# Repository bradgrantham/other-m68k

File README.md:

# other-m68k

A complete homebrew 68000 single-board computer: hardware, glue logic, firmware, SDK and
emulator, all generated from one specification.

| | |
|---|---|
| CPU | MC68000 at 12 MHz (24 MHz oscillator divided in the glue) |
| RAM | 1 MB: 2x AS6C4008-55PCN 512Kx8 SRAM, word wide, time-sliced with the video fetch |
| ROM | 1 MB window: 2x SST39SF040 flash, word wide; 256 KB BIOS image (in-system programmable, overlaid at address 0 at reset) plus a 768 KB FAT12 volume the BIOS mounts as drive C: |
| Video | memory-mapped 320x240, 8 bpp RGB332 framebuffer, two pages; AD724 encoder with composite and S-video outputs, NTSC (PAL by build option) |
| Glue | two ATF1508AS CPLDs ("MMU" and "I/O + shifter"), two 74AHCT245 bus transceivers |
| I/O | PS/2 keyboard, Atari joystick/paddle port (DE-9 on the DUART's I/O pins), microSD card on a bit-banged 4-bit SD bus, 68681 DUART serial on two FTDI headers (channel A at 38400 8N1 carries the POST and banner, then belongs to programs as `/dev/ttya`; channel B is free), 8-bit PDM audio (one byte per video line shifted out by the CPLD), 2 LEDs, NMI button |
| Power | USB-C, 5 V |

## Layout

| path | contents |
|---|---|
| `spec/board.json` | **the single source of truth**: memory map, registers, interrupts, video timing, syscalls, ABI |
| `tools/gen.py` | generates everything in `generated/` from the spec (`make gen`; `make check-gen` in CI) |
| `generated/` | C/asm headers, linker scripts, Verilog parameters, syscall stubs/dispatcher, emulator tables, `HARDWARE.md` |
| `docs/architecture.md` | the bus-timing contract: slot schedule, decode, alignment, peripherals |
| `docs/bringup.md` | staged hardware bring-up plan |
| `docs/programmers-guide.md` | programmer's guide: writing applications with the SDK, and programming the hardware directly |
| `hdl/` | Verilog for both CPLDs plus a system testbench with a 68000 bus model |
| `emu/` | SDL2 emulator (Musashi 68000 core), used to run the firmware and user programs |
| `fw/` | BIOS/monitor ROM: POST, serial, video console, PS/2, exceptions, monitor (drives C: and D:, scripts, AUTOEXEC.CMD), syscalls, FatFs with long names, flash volume driver, clock, ELF loader |
| `sdk/` | user-program crt0, linker script, syscall library, newlib shim, examples |
| `flashfs/` | the files that go into the C: volume besides the SDK examples (AUTOEXEC.CMD, README.TXT) |
| `kicad/` | generated schematic and PCB |

## Building

```
make gen        # regenerate from the spec
make fw         # fw/build/rom.bin (256 KB BIOS image, for the monitor's `flash` command)
make flash      # fw/build/flash.img (BIOS + the C: volume from flashfs/ and the SDK examples), rom_even.bin / rom_odd.bin for the two flash chips
make emu        # emu/build/m68k-emu
make sdk        # sdk/build/*.elf user programs
make run        # boot flash.img in the emulator (what the machine writes to C: persists in it)
make -C hdl sim # simulate the glue logic (needs iverilog)
```

Cross toolchain: `~/x-tools/m68k-unknown-elf` (crosstool-ng, GCC 15, `--with-cpu=68000`,
newlib). Override with `XTOOLS=/path/to/bin`.

## How the pieces fit

The spec names every address and bit once. `tools/gen.py` turns it into `hw.h` for C, `hw.inc`
for assembler, `board_params.vh` for the CPLDs, `emu_map.h` for the emulator and `HARDWARE.md`
for humans, plus syscall stubs for user programs and the dispatcher for the BIOS. Changing the
memory map or adding a syscall is one edit followed by `make gen`.

`docs/architecture.md` explains the mechanism the numbers describe: the SRAM is shared on a
fixed 4-clock slot, video takes the first half, the CPU the second, and CPU cycles are
phase-aligned by delaying DTACK by zero or two clocks. The video fetch therefore never costs
the CPU a bus slot.

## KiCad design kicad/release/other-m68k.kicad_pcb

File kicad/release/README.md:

# other-m68k release snapshot

Generated by `make -C kicad board route fab release` from the commit that last touched this directory.

- `other-m68k.kicad_pro` + `*.kicad_sch`: the schematic (open the .kicad_pro in KiCad 9; libraries resolve via ../lib)
- `other-m68k.kicad_pcb`: the **routed** board (DRC clean, 0 unrouted)
- `other-m68k-schematic.pdf`, `other-m68k-placement.svg`, `other-m68k-routed.svg`: for review without KiCad
- `fab/`: what PCBWay gets: `other-m68k-gerbers.zip`, `other-m68k-pcbway-bom.csv`, `other-m68k-pcbway-centroid.csv`;
  plus `other-m68k-customer-parts.csv` (what we fit), `other-m68k-bom-check.txt`, generic/JLCPCB BOMs

See ../ORDER.md for the order parameters.

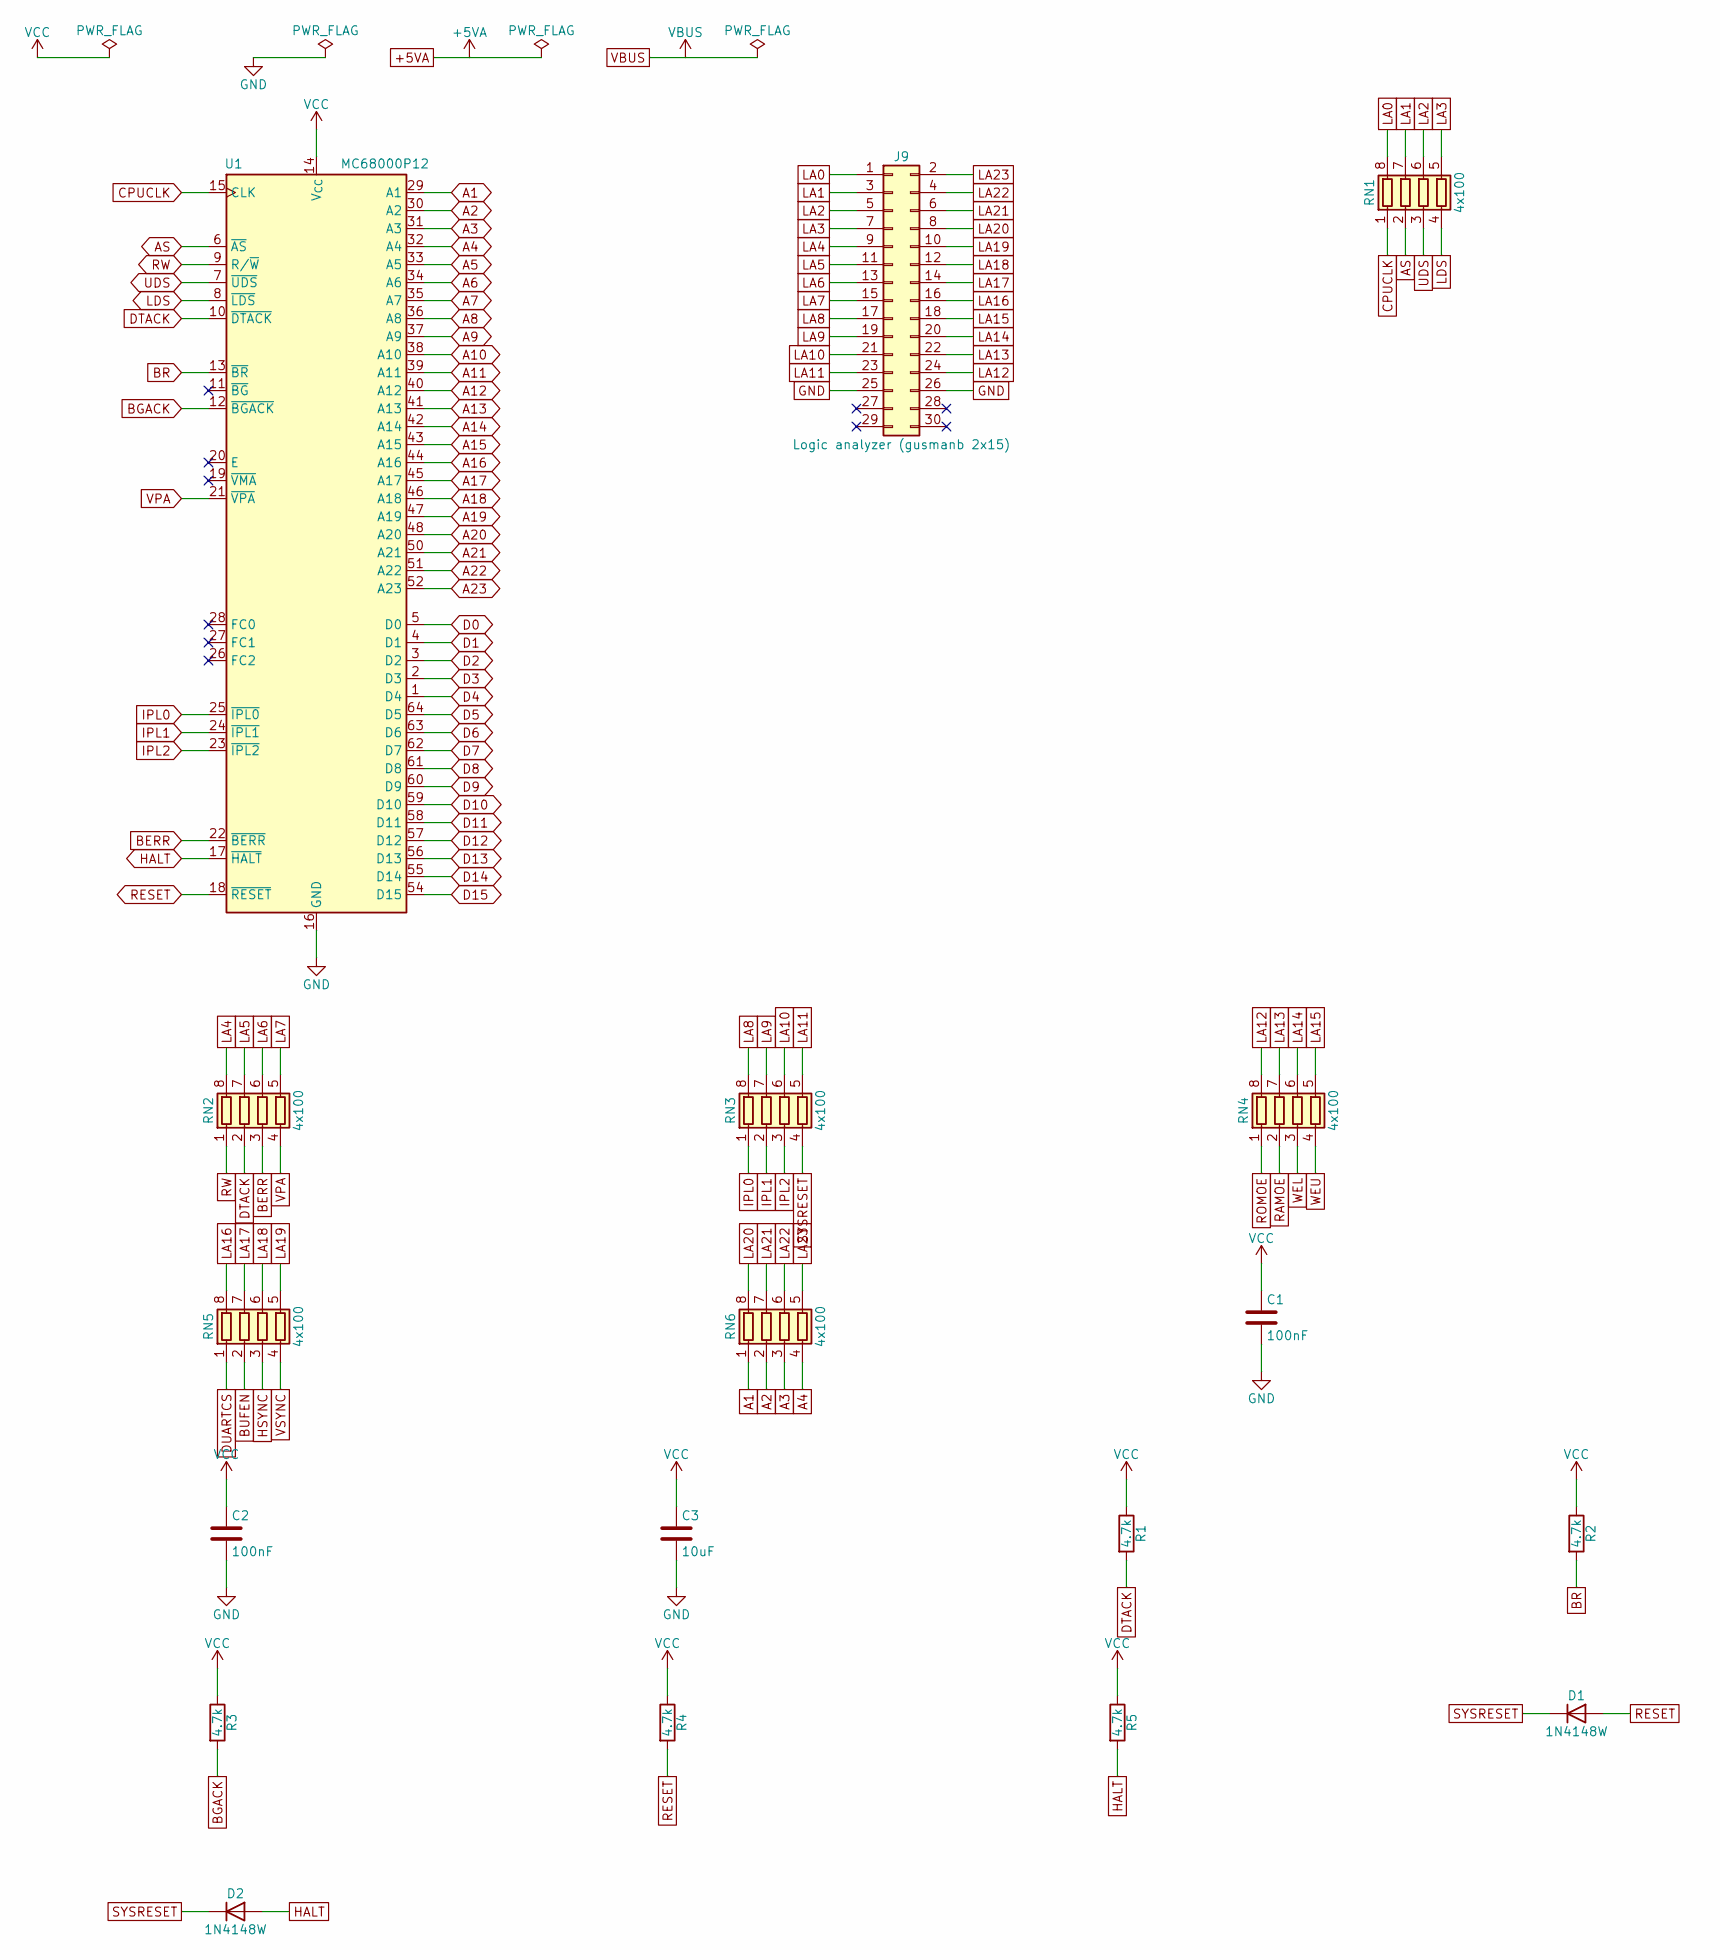
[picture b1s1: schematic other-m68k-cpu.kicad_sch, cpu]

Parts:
C1, C2: 100nF; C_0603_1608Metric; MPN CL10B104KB8NNNC; LCSC C1591
C3: 10uF; C_0805_2012Metric; MPN CL21A106KAYNNNE; LCSC C15850
D1, D2: 1N4148W; D_SOD-123; MPN 1N4148W-7-F; LCSC C81598
J9: Logic analyzer (gusmanb 2x15); PinHeader_2x15_P2.54mm_Vertical; MPN PRPC015DAAN-RC
R1, R2, R3, R4, R5: 4.7k; R_0603_1608Metric; MPN RC0603FR-074K7L; LCSC C23162
RN1, RN2, RN3, RN4, RN5, RN6: 4x100; R_Array_Convex_4x0603; MPN YC164-JR-07100RL
U1: MC68000P12; DIP-64_W22.86mm_Socket; MPN MC68000P12

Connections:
A1: RN6.1 (R1.1), U1.29 (A1); also elsewhere on the board
A2: RN6.2 (R2.1), U1.30 (A2); also elsewhere on the board
A3: RN6.3 (R3.1), U1.31 (A3); also elsewhere on the board
A4: RN6.4 (R4.1), U1.32 (A4); also elsewhere on the board
A5: U1.33 (A5); also elsewhere on the board
A6: U1.34 (A6); also elsewhere on the board
A7: U1.35 (A7); also elsewhere on the board
A8: U1.36 (A8); also elsewhere on the board
A9: U1.37 (A9); also elsewhere on the board
A10: U1.38 (A10); also elsewhere on the board
A11: U1.39 (A11); also elsewhere on the board
A12: U1.40 (A12); also elsewhere on the board
A13: U1.41 (A13); also elsewhere on the board
A14: U1.42 (A14); also elsewhere on the board
A15: U1.43 (A15); also elsewhere on the board
A16: U1.44 (A16); also elsewhere on the board
A17: U1.45 (A17); also elsewhere on the board
A18: U1.46 (A18); also elsewhere on the board
A19: U1.47 (A19); also elsewhere on the board
A20: U1.48 (A20); also elsewhere on the board
A21: U1.50 (A21); also elsewhere on the board
A22: U1.51 (A22); also elsewhere on the board
A23: U1.52 (A23); also elsewhere on the board
AS: RN1.2 (R2.1), U1.6 (~AS); also elsewhere on the board
BERR: RN2.3 (R3.1), U1.22 (~BERR); also elsewhere on the board
BGACK: R3.2, U1.12 (~BGACK)
BR: R2.2, U1.13 (~BR)
BUFEN: RN5.2 (R2.1); also elsewhere on the board
CPUCLK: RN1.1 (R1.1), U1.15 (CLK); also elsewhere on the board
D0: U1.5 (D0); also elsewhere on the board
D1: U1.4 (D1); also elsewhere on the board
D2: U1.3 (D2); also elsewhere on the board
D3: U1.2 (D3); also elsewhere on the board
D4: U1.1 (D4); also elsewhere on the board
D5: U1.64 (D5); also elsewhere on the board
D6: U1.63 (D6); also elsewhere on the board
D7: U1.62 (D7); also elsewhere on the board
D8: U1.61 (D8); also elsewhere on the board
D9: U1.60 (D9); also elsewhere on the board
D10: U1.59 (D10); also elsewhere on the board
D11: U1.58 (D11); also elsewhere on the board
D12: U1.57 (D12); also elsewhere on the board
D13: U1.56 (D13); also elsewhere on the board
D14: U1.55 (D14); also elsewhere on the board
D15: U1.54 (D15); also elsewhere on the board
DTACK: R1.2, RN2.2 (R2.1), U1.10 (~DTACK); also elsewhere on the board
DUARTCS: RN5.1 (R1.1); also elsewhere on the board
GND: C1.2, C2.2, C3.2, J9.25, J9.26, U1.16 (GND), U1.53 (GND); also elsewhere on the board
HALT: D2.2 (A), R5.2, U1.17 (~HALT)
HSYNC: RN5.3 (R3.1); also elsewhere on the board
IPL0: RN3.1 (R1.1), U1.25 (~IPL0); also elsewhere on the board
IPL1: RN3.2 (R2.1), U1.24 (~IPL1); also elsewhere on the board
IPL2: RN3.3 (R3.1), U1.23 (~IPL2); also elsewhere on the board
LA0: J9.1, RN1.8 (R1.2)
LA1: J9.3, RN1.7 (R2.2)
LA2: J9.5, RN1.6 (R3.2)
LA3: J9.7, RN1.5 (R4.2)
LA4: J9.9, RN2.8 (R1.2)
LA5: J9.11, RN2.7 (R2.2)
LA6: J9.13, RN2.6 (R3.2)
LA7: J9.15, RN2.5 (R4.2)
LA8: J9.17, RN3.8 (R1.2)
LA9: J9.19, RN3.7 (R2.2)
LA10: J9.21, RN3.6 (R3.2)
LA11: J9.23, RN3.5 (R4.2)
LA12: J9.24, RN4.8 (R1.2)
LA13: J9.22, RN4.7 (R2.2)
LA14: J9.20, RN4.6 (R3.2)
LA15: J9.18, RN4.5 (R4.2)
LA16: J9.16, RN5.8 (R1.2)
LA17: J9.14, RN5.7 (R2.2)
LA18: J9.12, RN5.6 (R3.2)
LA19: J9.10, RN5.5 (R4.2)
LA20: J9.8, RN6.8 (R1.2)
LA21: J9.6, RN6.7 (R2.2)
LA22: J9.4, RN6.6 (R3.2)
LA23: J9.2, RN6.5 (R4.2)
LDS: RN1.4 (R4.1), U1.8 (~LDS); also elsewhere on the board
RAMOE: RN4.2 (R2.1); also elsewhere on the board
RESET: D1.2 (A), R4.2, U1.18 (~RESET)
ROMOE: RN4.1 (R1.1); also elsewhere on the board
RW: RN2.1 (R1.1), U1.9 (R/~W); also elsewhere on the board
SYSRESET: D1.1 (K), D2.1 (K), RN3.4 (R4.1); also elsewhere on the board
UDS: RN1.3 (R3.1), U1.7 (~UDS); also elsewhere on the board
VCC: C1.1, C2.1, C3.1, R1.1, R2.1, R3.1, R4.1, R5.1, U1.14 (V_{CC}), U1.49 (V_{CC}); also elsewhere on the board
VPA: RN2.4 (R4.1), U1.21 (~VPA); also elsewhere on the board
VSYNC: RN5.4 (R4.1); also elsewhere on the board
WEL: RN4.3 (R3.1); also elsewhere on the board
WEU: RN4.4 (R4.1); also elsewhere on the board

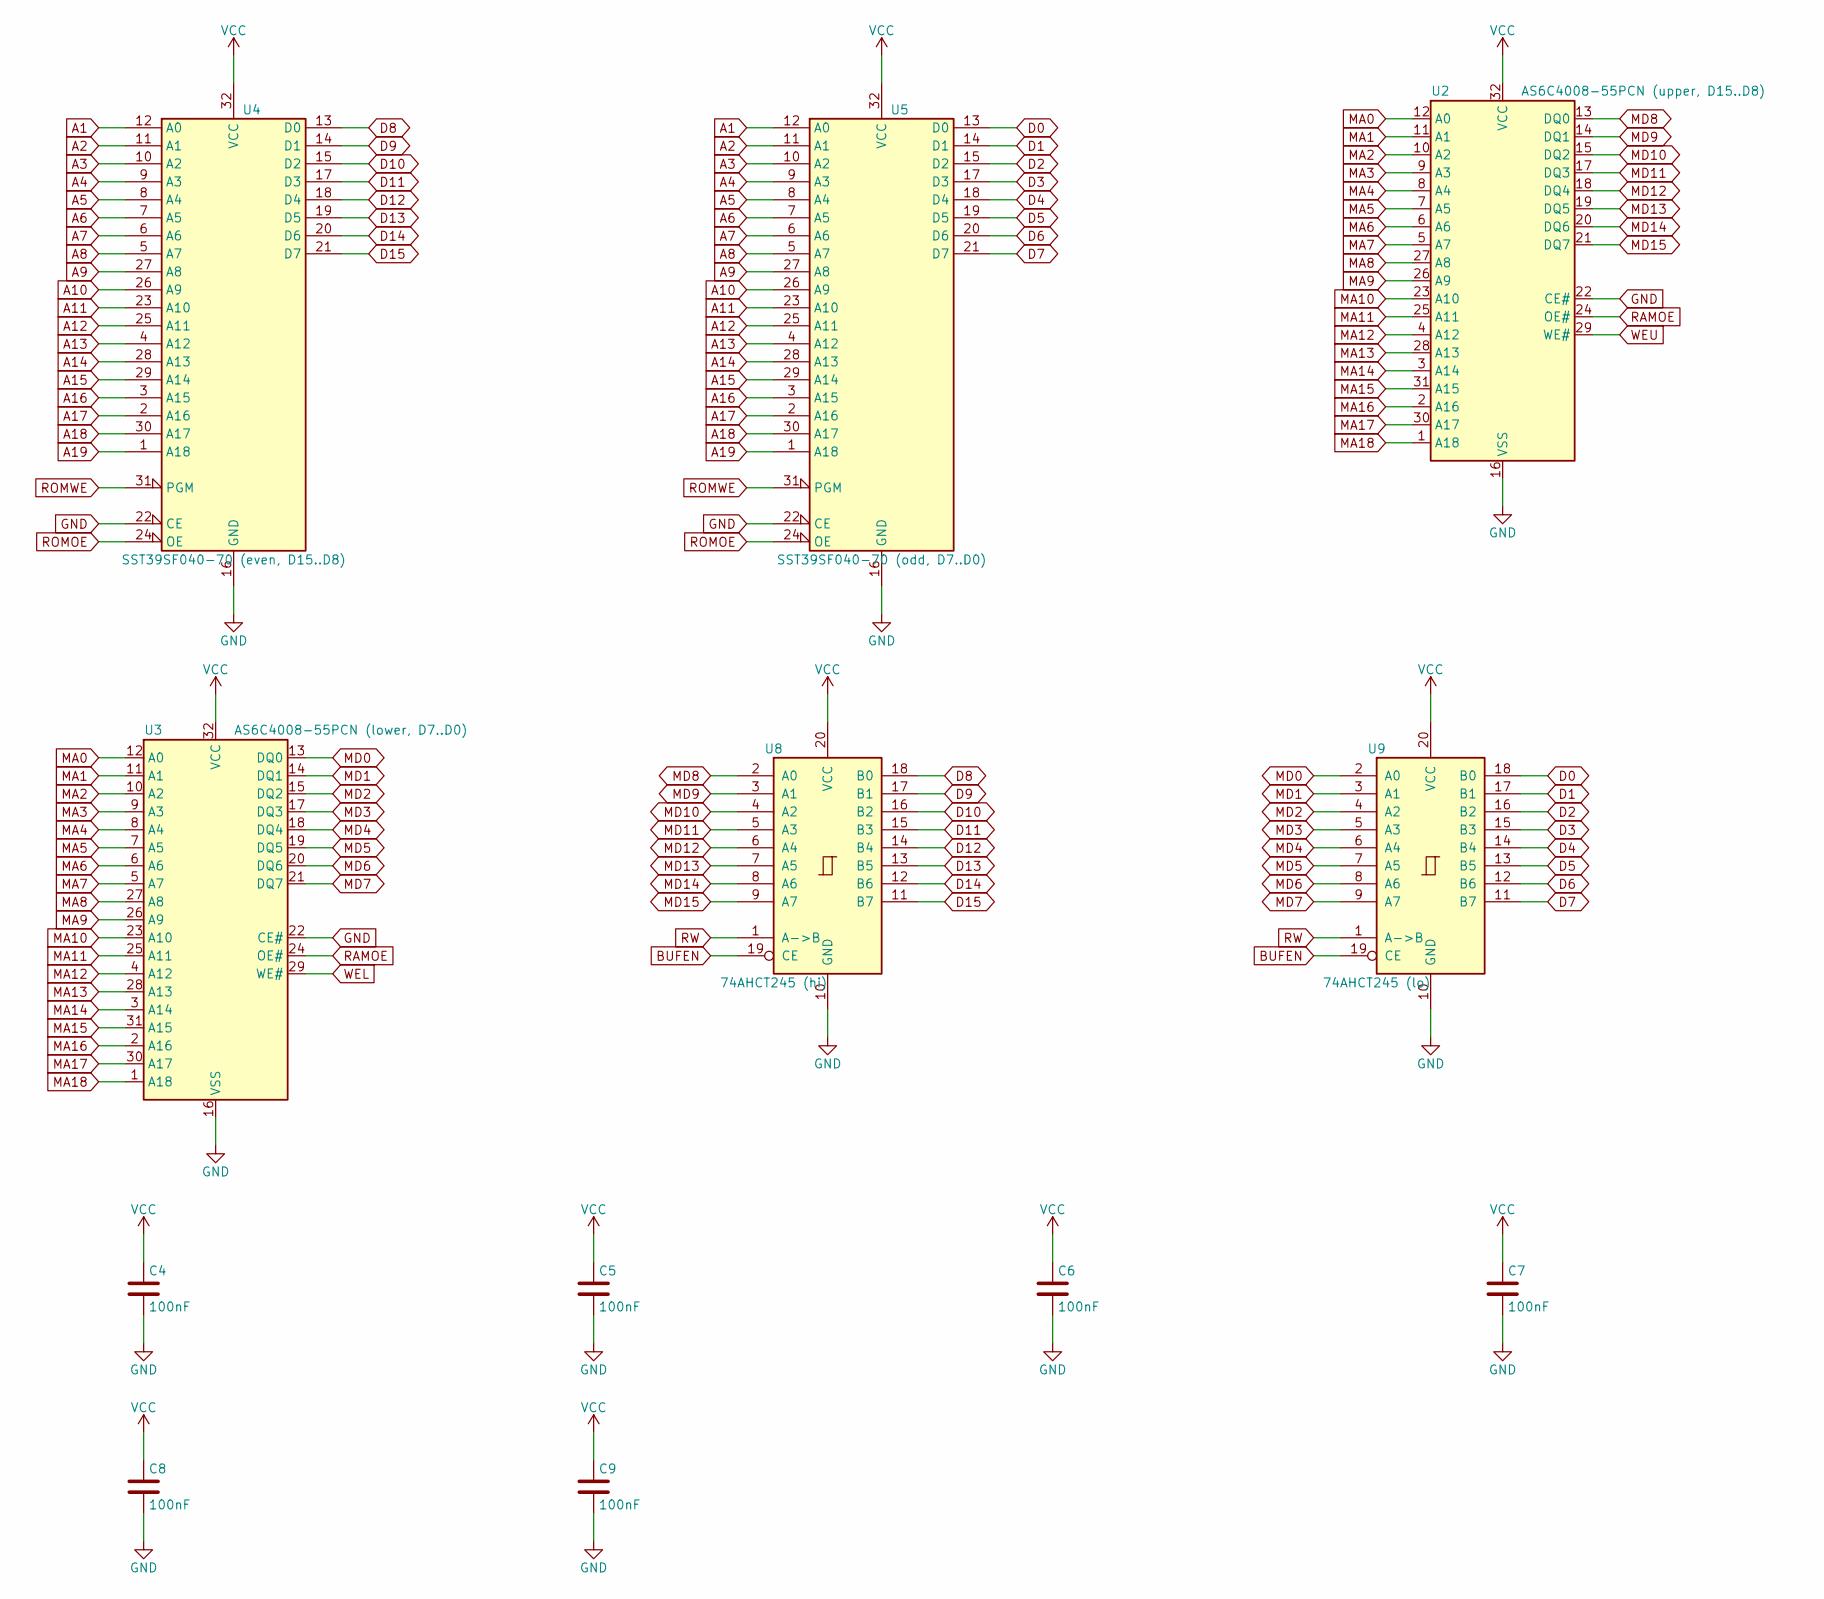
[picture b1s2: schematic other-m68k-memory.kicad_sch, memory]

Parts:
C4, C5, C6, C7, C8, C9: 100nF; C_0603_1608Metric; MPN CL10B104KB8NNNC; LCSC C1591
U2: AS6C4008-55PCN (upper, D15..D8); DIP-32_W15.24mm_Socket; MPN AS6C4008-55PCN
U3: AS6C4008-55PCN (lower, D7..D0); DIP-32_W15.24mm_Socket; MPN AS6C4008-55PCN
U4: SST39SF040-70 (even, D15..D8); DIP-32_W15.24mm_Socket; MPN SST39SF040-70-4C-PHE
U5: SST39SF040-70 (odd, D7..D0); DIP-32_W15.24mm_Socket; MPN SST39SF040-70-4C-PHE
U8: 74AHCT245 (hi); SOIC-20W_7.5x12.8mm_P1.27mm; MPN SN74AHCT245DW
U9: 74AHCT245 (lo); SOIC-20W_7.5x12.8mm_P1.27mm; MPN SN74AHCT245DW

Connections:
A1: U4.12 (A0), U5.12 (A0); also elsewhere on the board
A2: U4.11 (A1), U5.11 (A1); also elsewhere on the board
A3: U4.10 (A2), U5.10 (A2); also elsewhere on the board
A4: U4.9 (A3), U5.9 (A3); also elsewhere on the board
A5: U4.8 (A4), U5.8 (A4); also elsewhere on the board
A6: U4.7 (A5), U5.7 (A5); also elsewhere on the board
A7: U4.6 (A6), U5.6 (A6); also elsewhere on the board
A8: U4.5 (A7), U5.5 (A7); also elsewhere on the board
A9: U4.27 (A8), U5.27 (A8); also elsewhere on the board
A10: U4.26 (A9), U5.26 (A9); also elsewhere on the board
A11: U4.23 (A10), U5.23 (A10); also elsewhere on the board
A12: U4.25 (A11), U5.25 (A11); also elsewhere on the board
A13: U4.4 (A12), U5.4 (A12); also elsewhere on the board
A14: U4.28 (A13), U5.28 (A13); also elsewhere on the board
A15: U4.29 (A14), U5.29 (A14); also elsewhere on the board
A16: U4.3 (A15), U5.3 (A15); also elsewhere on the board
A17: U4.2 (A16), U5.2 (A16); also elsewhere on the board
A18: U4.30 (A17), U5.30 (A17); also elsewhere on the board
A19: U4.1 (A18), U5.1 (A18); also elsewhere on the board
BUFEN: U8.19 (CE), U9.19 (CE); also elsewhere on the board
D0: U5.13 (D0), U9.18 (B0); also elsewhere on the board
D1: U5.14 (D1), U9.17 (B1); also elsewhere on the board
D2: U5.15 (D2), U9.16 (B2); also elsewhere on the board
D3: U5.17 (D3), U9.15 (B3); also elsewhere on the board
D4: U5.18 (D4), U9.14 (B4); also elsewhere on the board
D5: U5.19 (D5), U9.13 (B5); also elsewhere on the board
D6: U5.20 (D6), U9.12 (B6); also elsewhere on the board
D7: U5.21 (D7), U9.11 (B7); also elsewhere on the board
D8: U4.13 (D0), U8.18 (B0); also elsewhere on the board
D9: U4.14 (D1), U8.17 (B1); also elsewhere on the board
D10: U4.15 (D2), U8.16 (B2); also elsewhere on the board
D11: U4.17 (D3), U8.15 (B3); also elsewhere on the board
D12: U4.18 (D4), U8.14 (B4); also elsewhere on the board
D13: U4.19 (D5), U8.13 (B5); also elsewhere on the board
D14: U4.20 (D6), U8.12 (B6); also elsewhere on the board
D15: U4.21 (D7), U8.11 (B7); also elsewhere on the board
GND: C4.2, C5.2, C6.2, C7.2, C8.2, C9.2, U2.16 (VSS), U2.22 (CE#), U3.16 (VSS), U3.22 (CE#), U4.16 (GND), U4.22 (CE), U5.16 (GND), U5.22 (CE), U8.10 (GND), U9.10 (GND); also elsewhere on the board
MA0: U2.12 (A0), U3.12 (A0); also elsewhere on the board
MA1: U2.11 (A1), U3.11 (A1); also elsewhere on the board
MA2: U2.10 (A2), U3.10 (A2); also elsewhere on the board
MA3: U2.9 (A3), U3.9 (A3); also elsewhere on the board
MA4: U2.8 (A4), U3.8 (A4); also elsewhere on the board
MA5: U2.7 (A5), U3.7 (A5); also elsewhere on the board
MA6: U2.6 (A6), U3.6 (A6); also elsewhere on the board
MA7: U2.5 (A7), U3.5 (A7); also elsewhere on the board
MA8: U2.27 (A8), U3.27 (A8); also elsewhere on the board
MA9: U2.26 (A9), U3.26 (A9); also elsewhere on the board
MA10: U2.23 (A10), U3.23 (A10); also elsewhere on the board
MA11: U2.25 (A11), U3.25 (A11); also elsewhere on the board
MA12: U2.4 (A12), U3.4 (A12); also elsewhere on the board
MA13: U2.28 (A13), U3.28 (A13); also elsewhere on the board
MA14: U2.3 (A14), U3.3 (A14); also elsewhere on the board
MA15: U2.31 (A15), U3.31 (A15); also elsewhere on the board
MA16: U2.2 (A16), U3.2 (A16); also elsewhere on the board
MA17: U2.30 (A17), U3.30 (A17); also elsewhere on the board
MA18: U2.1 (A18), U3.1 (A18); also elsewhere on the board
MD0: U3.13 (DQ0), U9.2 (A0); also elsewhere on the board
MD1: U3.14 (DQ1), U9.3 (A1); also elsewhere on the board
MD2: U3.15 (DQ2), U9.4 (A2); also elsewhere on the board
MD3: U3.17 (DQ3), U9.5 (A3); also elsewhere on the board
MD4: U3.18 (DQ4), U9.6 (A4); also elsewhere on the board
MD5: U3.19 (DQ5), U9.7 (A5); also elsewhere on the board
MD6: U3.20 (DQ6), U9.8 (A6); also elsewhere on the board
MD7: U3.21 (DQ7), U9.9 (A7); also elsewhere on the board
MD8: U2.13 (DQ0), U8.2 (A0); also elsewhere on the board
MD9: U2.14 (DQ1), U8.3 (A1); also elsewhere on the board
MD10: U2.15 (DQ2), U8.4 (A2); also elsewhere on the board
MD11: U2.17 (DQ3), U8.5 (A3); also elsewhere on the board
MD12: U2.18 (DQ4), U8.6 (A4); also elsewhere on the board
MD13: U2.19 (DQ5), U8.7 (A5); also elsewhere on the board
MD14: U2.20 (DQ6), U8.8 (A6); also elsewhere on the board
MD15: U2.21 (DQ7), U8.9 (A7); also elsewhere on the board
RAMOE: U2.24 (OE#), U3.24 (OE#); also elsewhere on the board
ROMOE: U4.24 (OE), U5.24 (OE); also elsewhere on the board
ROMWE: U4.31 (PGM), U5.31 (PGM); also elsewhere on the board
RW: U8.1 (A->B), U9.1 (A->B); also elsewhere on the board
VCC: C4.1, C5.1, C6.1, C7.1, C8.1, C9.1, U2.32 (VCC), U3.32 (VCC), U4.32 (VCC), U5.32 (VCC), U8.20 (VCC), U9.20 (VCC); also elsewhere on the board
WEL: U3.29 (WE#); also elsewhere on the board
WEU: U2.29 (WE#); also elsewhere on the board

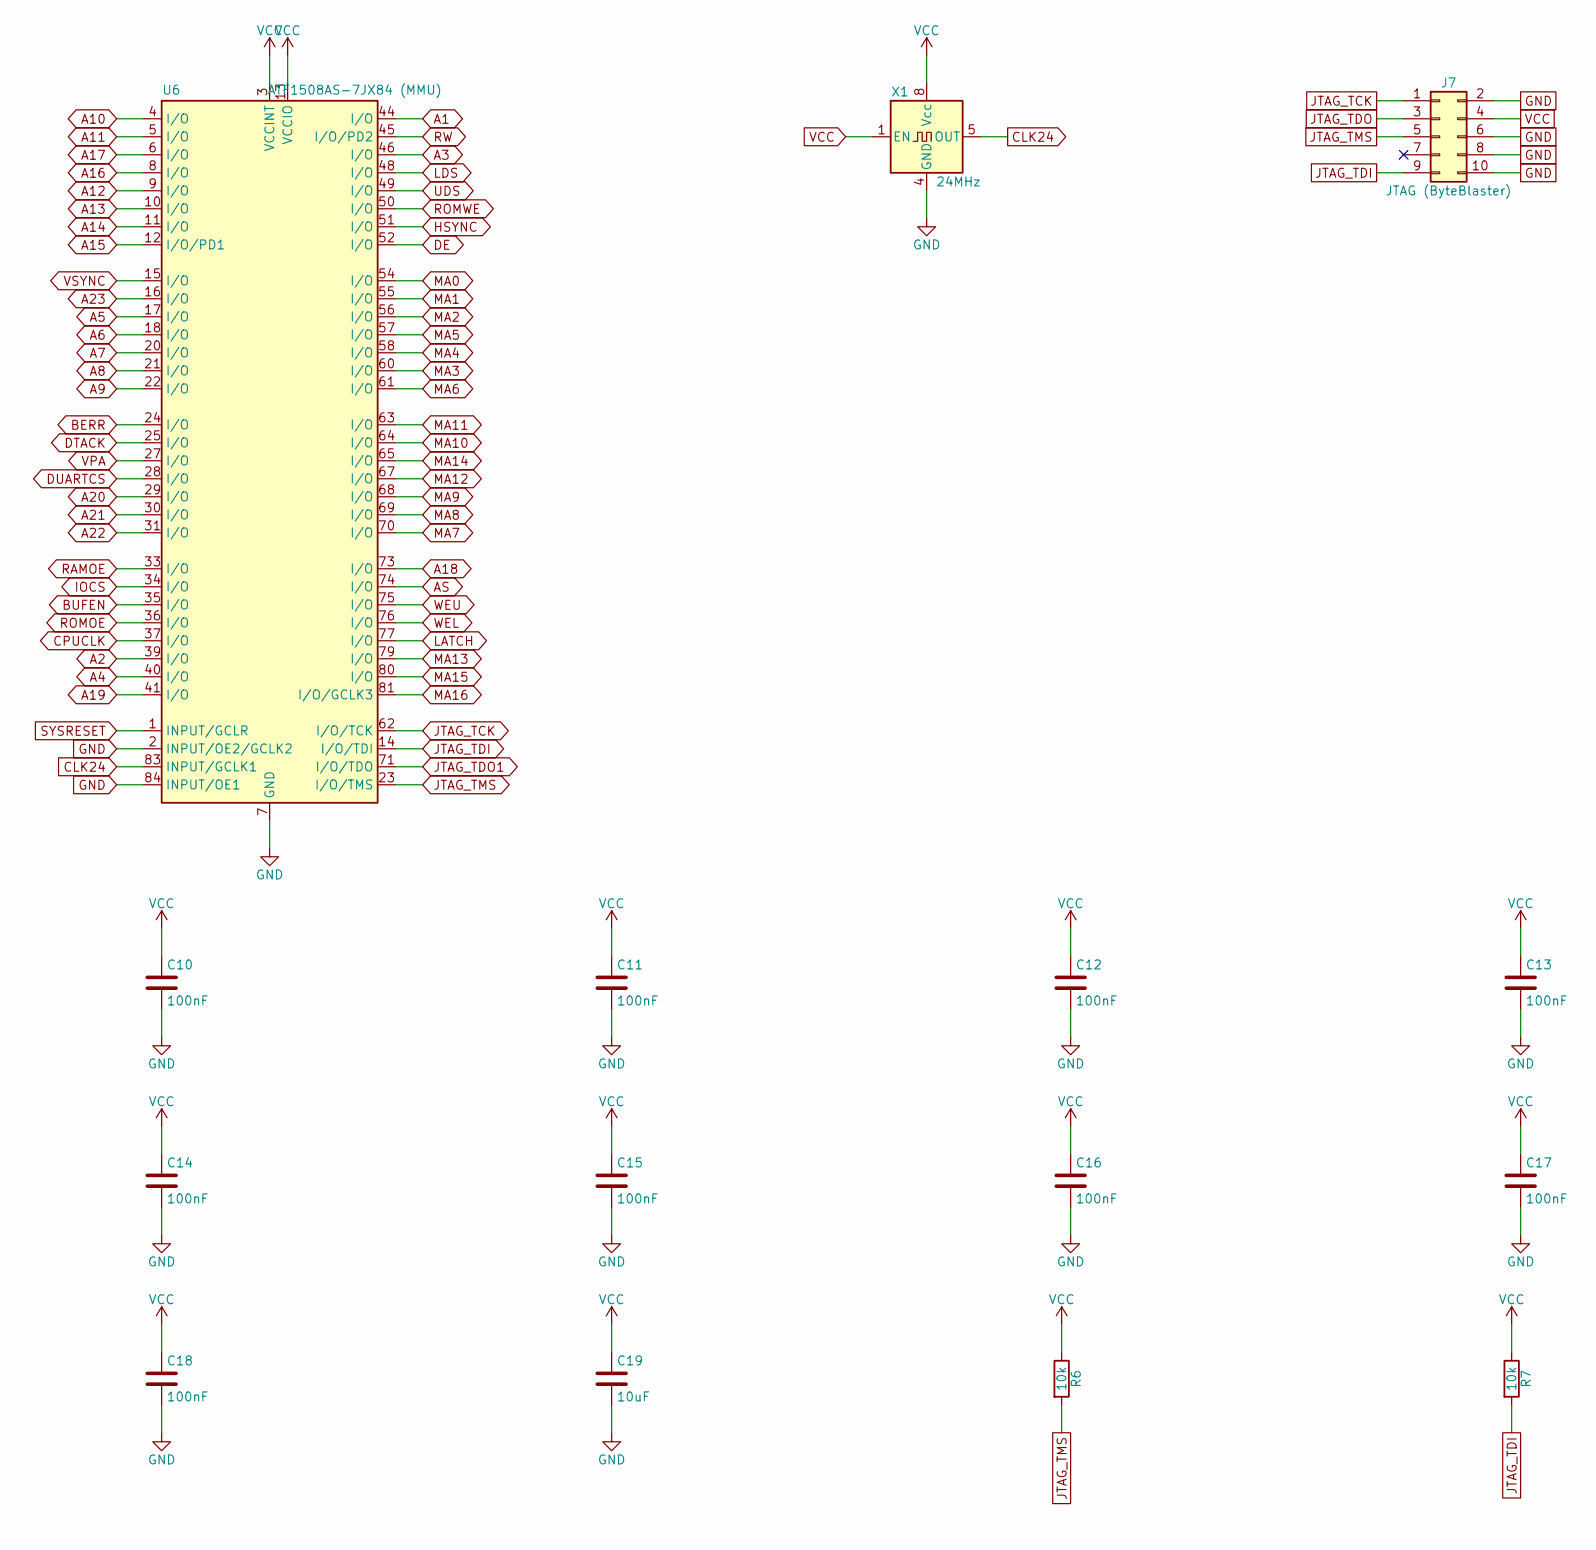
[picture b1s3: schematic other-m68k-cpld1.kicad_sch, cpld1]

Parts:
C10, C11, C12, C13, C14, C15, C16, C17, C18: 100nF; C_0603_1608Metric; MPN CL10B104KB8NNNC; LCSC C1591
C19: 10uF; C_0805_2012Metric; MPN CL21A106KAYNNNE; LCSC C15850
J7: JTAG (ByteBlaster); PinHeader_2x05_P2.54mm_Vertical; MPN PRPC005DAAN-RC
R6, R7: 10k; R_0603_1608Metric; MPN RC0603FR-0710KL; LCSC C25804
U6: ATF1508AS-7JX84 (MMU); PLCC-84_THT-Socket; MPN ATF1508AS-7JX84
X1: 24MHz; Oscillator_DIP-8; MPN ECS-2200B-240

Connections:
A1: U6.44 (I/O); also elsewhere on the board
A2: U6.39 (I/O); also elsewhere on the board
A3: U6.46 (I/O); also elsewhere on the board
A4: U6.40 (I/O); also elsewhere on the board
A5: U6.17 (I/O); also elsewhere on the board
A6: U6.18 (I/O); also elsewhere on the board
A7: U6.20 (I/O); also elsewhere on the board
A8: U6.21 (I/O); also elsewhere on the board
A9: U6.22 (I/O); also elsewhere on the board
A10: U6.4 (I/O); also elsewhere on the board
A11: U6.5 (I/O); also elsewhere on the board
A12: U6.9 (I/O); also elsewhere on the board
A13: U6.10 (I/O); also elsewhere on the board
A14: U6.11 (I/O); also elsewhere on the board
A15: U6.12 (I/O/PD1); also elsewhere on the board
A16: U6.8 (I/O); also elsewhere on the board
A17: U6.6 (I/O); also elsewhere on the board
A18: U6.73 (I/O); also elsewhere on the board
A19: U6.41 (I/O); also elsewhere on the board
A20: U6.29 (I/O); also elsewhere on the board
A21: U6.30 (I/O); also elsewhere on the board
A22: U6.31 (I/O); also elsewhere on the board
A23: U6.16 (I/O); also elsewhere on the board
AS: U6.74 (I/O); also elsewhere on the board
BERR: U6.24 (I/O); also elsewhere on the board
BUFEN: U6.35 (I/O); also elsewhere on the board
CLK24: U6.83 (INPUT/GCLK1), X1.5 (OUT); also elsewhere on the board
CPUCLK: U6.37 (I/O); also elsewhere on the board
DE: U6.52 (I/O); also elsewhere on the board
DTACK: U6.25 (I/O); also elsewhere on the board
DUARTCS: U6.28 (I/O); also elsewhere on the board
GND: C10.2, C11.2, C12.2, C13.2, C14.2, C15.2, C16.2, C17.2, C18.2, C19.2, J7.2, J7.6, J7.8, J7.10, U6.2 (INPUT/OE2/GCLK2), U6.7 (GND), U6.19 (GND), U6.32 (GND), U6.42 (GND), U6.47 (GND), U6.59 (GND), U6.72 (GND), U6.82 (GND), U6.84 (INPUT/OE1), X1.4 (GND); also elsewhere on the board
HSYNC: U6.51 (I/O); also elsewhere on the board
IOCS: U6.34 (I/O); also elsewhere on the board
JTAG_TCK: J7.1, U6.62 (I/O/TCK); also elsewhere on the board
JTAG_TDI: J7.9, R7.2, U6.14 (I/O/TDI)
JTAG_TDO: J7.3; also elsewhere on the board
JTAG_TDO1: U6.71 (I/O/TDO); also elsewhere on the board
JTAG_TMS: J7.5, R6.2, U6.23 (I/O/TMS); also elsewhere on the board
LATCH: U6.77 (I/O); also elsewhere on the board
LDS: U6.48 (I/O); also elsewhere on the board
MA0: U6.54 (I/O); also elsewhere on the board
MA1: U6.55 (I/O); also elsewhere on the board
MA2: U6.56 (I/O); also elsewhere on the board
MA3: U6.60 (I/O); also elsewhere on the board
MA4: U6.58 (I/O); also elsewhere on the board
MA5: U6.57 (I/O); also elsewhere on the board
MA6: U6.61 (I/O); also elsewhere on the board
MA7: U6.70 (I/O); also elsewhere on the board
MA8: U6.69 (I/O); also elsewhere on the board
MA9: U6.68 (I/O); also elsewhere on the board
MA10: U6.64 (I/O); also elsewhere on the board
MA11: U6.63 (I/O); also elsewhere on the board
MA12: U6.67 (I/O); also elsewhere on the board
MA13: U6.79 (I/O); also elsewhere on the board
MA14: U6.65 (I/O); also elsewhere on the board
MA15: U6.80 (I/O); also elsewhere on the board
MA16: U6.81 (I/O/GCLK3); also elsewhere on the board
RAMOE: U6.33 (I/O); also elsewhere on the board
ROMOE: U6.36 (I/O); also elsewhere on the board
ROMWE: U6.50 (I/O); also elsewhere on the board
RW: U6.45 (I/O/PD2); also elsewhere on the board
SYSRESET: U6.1 (INPUT/GCLR); also elsewhere on the board
UDS: U6.49 (I/O); also elsewhere on the board
VCC: C10.1, C11.1, C12.1, C13.1, C14.1, C15.1, C16.1, C17.1, C18.1, C19.1, J7.4, R6.1, R7.1, U6.3 (VCCINT), U6.13 (VCCIO), U6.26 (VCCIO), U6.38 (VCCIO), U6.43 (VCCINT), U6.53 (VCCIO), U6.66 (VCCIO), U6.78 (VCCIO), X1.1 (EN), X1.8 (Vcc); also elsewhere on the board
VPA: U6.27 (I/O); also elsewhere on the board
VSYNC: U6.15 (I/O); also elsewhere on the board
WEL: U6.76 (I/O); also elsewhere on the board
WEU: U6.75 (I/O); also elsewhere on the board

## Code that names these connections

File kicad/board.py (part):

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
    # ------------------------------------------------------------------ CPU control
    b.net("AS", u1.pin("AS"), u6.pin(p1["AS"]))
    b.net("UDS", u1.pin("UDS"), u6.pin(p1["UDS"]))
    b.net("LDS", u1.pin("LDS"), u6.pin(p1["LDS"]))
    b.net("RW", u1.pin("R/W"), u6.pin(p1["RW"]), u7.pin(p2["RW"]), u10.pin("R/W"), u8.pin("A->B"), u9.pin("A->B"))
    r_dtack = R("4.7k", "cpu", near="U1")
    b.net("DTACK", u1.pin("DTACK"), u6.pin(p1["DTACK"]), u10.pin("DTACK"), r_dtack.pin(2))   # open-drain bus
    b.power("VCC", r_dtack.pin(1))
    b.net("BERR", u1.pin("BERR"), u6.pin(p1["BERR"]))
    b.net("VPA", u1.pin("VPA"), u6.pin(p1["VPA"]))
    b.net("CPUCLK", u1.pin("CLK"), u6.pin(p1["CPUCLK"]))
    for i in range(3):
        b.net(f"IPL{i}", u1.pin(f"IPL{i}"), u7.pin(p2[f"IPL{i}"]))
    for name in ("BR", "BGACK"):               # no bus masters: pulled high
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        d = b.part(dref, "Diode", "1N4148W", SOD123, "1N4148W", sheet="cpu", PcbNear="U1")
        b.net(name, u1.pin(name), r.pin(2), d.pin("A"))
        b.power("VCC", r.pin(1))
        b.net("SYSRESET", d.pin("K"))
    u1.nc("BG", "VMA", "E", "FC0", "FC1", "FC2")
    b.power("VCC", u1.pins("VCC"))             # 14 and the hidden stacked 49
    b.power("GND", u1.pins("GND"))             # 16 and the hidden stacked 53
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        b.power("GND", u.pin("CE#"))            # pin 22, active low: always enabled (OE/WE gate)
        b.power("VCC", u.pin("VCC"))
        b.power("GND", u.pin("VSS"))
    b.net("RAMOE", u6.pin(p1["RAMOE"]), u2.pin("OE#"), u3.pin("OE#"))
    b.net("WEU", u6.pin(p1["WEU"]), u2.pin("WE#"))
    b.net("WEL", u6.pin(p1["WEL"]), u3.pin("WE#"))
    for u in (u4, u5):
        b.power("GND", u.pin("CE"))             # CE tied low; OE/WE from CPLD1 do the gating
        b.power("VCC", u.pin("VCC"))
        b.power("GND", u.pin("GND"))
    b.net("ROMOE", u6.pin(p1["ROMOE"]), u4.pin("OE"), u5.pin("OE"))
    b.net("ROMWE", u6.pin(p1["ROMWE"]), u4.pin("PGM"), u5.pin("PGM"))   # pin 31 = /WE
    b.net("BUFEN", u6.pin(p1["BUFEN"]), u8.pin("CE"), u9.pin("CE"))   # pin 19 = OE on the '245
    for u in (u8, u9):
        b.power("VCC", u.pin("VCC"))
        b.power("GND", u.pin("GND"))
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        decouple(u, [u.pin("VCC").pin.number], "memory")

    # ------------------------------------------------------------------ CPLD1
    b.net("SYSRESET", u6.pin(p1["SYSRESET"]), u7.pin(p2["SYSRESET"]))          # GCLR, pin 1
    b.net("CLK24", x1.pin("OUT"), u6.pin(p1["CLK24"]), u7.pin(p2["CLK24"]))    # GCLK1, pin 83
    b.power("VCC", x1.pin("Vcc"), x1.pin("EN"))
    b.power("GND", x1.pin("GND"))
    decouple(x1, ["8"], "cpld1")
    for name in ("IOCS", "LATCH", "DE", "HSYNC", "VSYNC"):
        b.net(name, u6.pin(p1[name]), u7.pin(p2[name]))
    b.net("HSYNC", u11.pin("16"))              # AD724 HSYNC
    b.net("VSYNC", u11.pin("15"))              # AD724 VSYNC
    b.net("DUARTCS", u6.pin(p1["DUARTCS"]), u10.pin("CS"))
    for u, sheet in ((u6, "cpld1"), (u7, "cpld2")):
        b.power("VCC", u.pins("VCCINT"), u.pins("VCCIO"))   # 3,43 + 13,26,38,53,66,78 (stacked hidden)
        b.power("GND", u.pins("GND"))                        # 7,19,32,42,47,59,72,82
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        u.nc_unused = True
    # JTAG chain: header -> U6 -> U7 -> header.  TDI 14, TMS 23, TCK 62, TDO 71 on both.
    r_tms, r_tdi1, r_tdi2 = R("10k", "cpld1", near="U6"), R("10k", "cpld1", near="U6"), R("10k", "cpld2", near="U7")
    b.net("JTAG_TCK", j7.pin(1), u6.pin("62"), u7.pin("62"))
    b.net("JTAG_TMS", j7.pin(5), u6.pin("23"), u7.pin("23"), r_tms.pin(2))
    b.net("JTAG_TDI", j7.pin(9), u6.pin("14"), r_tdi1.pin(2))
    b.net("JTAG_TDO1", u6.pin("71"), u7.pin("14"), r_tdi2.pin(2))
    b.net("JTAG_TDO", u7.pin("71"), j7.pin(3))
    b.power("VCC", r_tms.pin(1), r_tdi1.pin(1), r_tdi2.pin(1), j7.pin(4))
    b.power("GND", j7.pin(2), j7.pin(6), j7.pin(8), j7.pin(10))
    j7.nc(7)

    # ------------------------------------------------------------------ CPLD2 peripherals
    # PS/2 (mini-DIN 6: 1 DATA, 3 GND, 4 VCC, 5 CLK; 2 and 6 unused)
    for name, pin in (("PS2_DAT", 1), ("PS2_CLK", 5)):
        r = R("4.7k", "cpld2", near="J3")
        b.net(name, u7.pin(p2[name]), j3.pin(pin), r.pin(2))
        b.power("VCC", r.pin(1))
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    # NMI button: active high, 10k pull-down, 100 nF debounce
    r = R("10k", "cpld2", near="SW2")
    c = C("100nF", "cpld2", near="SW2")
    b.net("NMIBTN", u7.pin(p2["NMIBTN"]), sw2.pin(2), r.pin(1), c.pin(1))
    b.power("GND", r.pin(2), c.pin(2))
    b.power("VCC", sw2.pin(1))
    # LEDs
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        b.power("GND", d.pin("K"))
    # DUART interrupt (open drain) into CPLD2
    r = R("4.7k", "io", near="U10")
    b.net("DUART_IRQ", u10.pin("IRQ"), u7.pin(p2["DUART_IRQ"]), r.pin(2))
    b.power("VCC", r.pin(1))
    # microSD, native 4-bit SD bus (spec rev 7): CLK, CMD and DAT0..3 go straight from CPLD2
    # to the card. CPLD2 drives each line open-drain (low or released) and reads it back, so
    # the 10 k pull-ups to +3V3 set the high level; no 5 V -> 3.3 V dividers (the card
    # answers on CMD and drives DAT0..3 during reads, which a divider would fight).
    for name, sdpin in (("SD_DAT3", "DAT3/CD"), ("SD_CLK", "CLK"), ("SD_CMD", "CMD"),
                        ("SD_DAT0", "DAT0"), ("SD_DAT1", "DAT1"), ("SD_DAT2", "DAT2")):
        r = R("10k", "cpld2", near="J4")
        b.net(name, u7.pin(p2[name]), j4.pin(sdpin), r.pin(2))
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    r_lp, c_lp = R("1k", "cpld2", near="J6"), C("33nF", "cpld2", near="J6")
    r_div1, r_div2 = R("10k", "cpld2", near="J6"), R("2.2k", "cpld2", near="J6")
    c_out = C("10uF", "cpld2", near="J6", fp=C0805)
    b.net("AUDIO", u7.pin(p2["AUDIO"]), r_lp.pin(1))
    b.net("AUDIO_LP", r_lp.pin(2), c_lp.pin(1), r_div1.pin(1))
    b.net("AUDIO_DIV", r_div1.pin(2), r_div2.pin(1), c_out.pin(1))
    b.net("AUDIO_OUT", c_out.pin(2), j6.pin("T"), j6.pin("R"))
    b.power("GND", c_lp.pin(2), r_div2.pin(2), j6.pin("S"))

    # ------------------------------------------------------------------ video (docs/video-encoder.md)
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    # NTSC only (decision 2026-10-20): STND pulled up through 10k, PALJMP (CPLD2 input) pulled
    # down through 10k; both resistors stay so a PAL board is a two-resistor mod, not a new layout
    r_stnd, r_pal = R("10k", "video", near="U11"), R("10k", "cpld2", near="U7")
    b.net("STND", u11.pin("1"), r_stnd.pin(2))
    b.power("VCC", r_stnd.pin(1))
    b.net("PALJMP", u7.pin(p2["PALJMP"]), r_pal.pin(1))
    b.power("GND", r_pal.pin(2))
    # subcarrier crystal on FIN with ~10 pF shunt; FSC mode (SELECT low via 10k); encode enabled
    c_fin = C("10pF", "video", near="Y2")
    b.net("FIN", u11.pin("3"), y2.pin(1), c_fin.pin(1))
    b.power("GND", y2.pin(2), c_fin.pin(2))
    r_sel = R("10k", "video", near="U11")
    b.net("SELECT", u11.pin("12"), r_sel.pin(1))
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    # composite out: 220 uF (+ at the chip) then 75 ohm series to the RCA centre
    c_comp = C("220uF", "video", near="J5", fp=CP_RADIAL, symbol="C_Polarized")
    r_ser = R("75", "video", near="J5")
    b.net("COMP", u11.pin("10"), c_comp.pin(1))
    b.net("COMP_AC", c_comp.pin(2), r_ser.pin(1))
    b.net("VIDEO", r_ser.pin(2), j5.pin(1))
    b.power("GND", j5.pin(2))
    # S-video (rev C2): LUMA and CRMA the same way, each 220 uF then 75 ohm, to the mini-DIN 4
    # (1 GND-Y, 2 GND-C, 3 Y, 4 C); the AD724 drives all three outputs at once
    c_y, c_c = C("220uF", "video", near="J10", fp=CP_RADIAL, symbol="C_Polarized"), C("220uF", "video", near="J10", fp=CP_RADIAL, symbol="C_Polarized")
    r_y, r_c = R("75", "video", near="J10"), R("75", "video", near="J10")
    b.net("LUMA", u11.pin("11"), c_y.pin(1))
    b.net("LUMA_AC", c_y.pin(2), r_y.pin(1))
    b.net("SVIDEO_Y", r_y.pin(2), j10.pin(3))
    b.net("CRMA", u11.pin("9"), c_c.pin(1))
    b.net("CRMA_AC", c_c.pin(2), r_c.pin(1))
    b.net("SVIDEO_C", r_c.pin(2), j10.pin(4))
    b.power("GND", j10.pin(1), j10.pin(2), j10.pin("SH"))
    # supplies: APOS through a ferrite bead (+5VA), DPOS from VCC, 100 nF + 10 uF each
    b.power("VCC", fb1.pin(1), u11.pin("14"))
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    b.power("GND", u11.pin("2"), u11.pin("13"))

    # ------------------------------------------------------------------ DUART, serial, reset
    b.net("SYSRESET", u10.pin("RESET"))
    r_iack = R("4.7k", "io", near="U10")
    b.net("DUART_IACK", u10.pin("IACK"), r_iack.pin(2))
    b.power("VCC", r_iack.pin(1))
    # crystal: 3.6864 MHz across X1/CLK and X2, 10-15 pF X1 to GND, 0-5 pF X2 to GND (optional)
    c_x1 = C("15pF", "io", near="Y1")
    c_x2 = C("DNP (0-5pF)", "io", near="Y1", dnp=True)
    b.net("DUART_X1", u10.pin("X1/CLK"), y1.pin(1), c_x1.pin(1))
    b.net("DUART_X2", u10.pin("X2"), y1.pin(2), c_x2.pin(1))
    b.power("GND", c_x1.pin(2), c_x2.pin(2))
    # channel A to the FTDI header J2 (1 GND, 2 CTS, 3 VCC, 4 TXD, 5 RXD, 6 RTS), channel B to
    # the identical J11 (rev C2; the 2x8 expansion header it replaces carried only these two
    # signals and the rails after spec rev 7). TTL levels, 5 V; CTS/RTS/VCC not connected.
    b.net("FTDI_TXD", j2.pin(4), u10.pin("RXDA"))
    b.net("FTDI_RXD", j2.pin(5), u10.pin("TXDA"))
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
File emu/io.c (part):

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 * region).  CPLD2 has no UDS/LDS, so byte accesses are undefined on the real
 * board; here a byte read returns its half of the word and a byte write
 * updates only that half of the shadow (the least surprising choice for
 * software).  INTEN, GPIO and AUDIO are write-only on the board (they read as 0);
 * the emulator keeps the written values as the pin state.  SDIO (spec rev 7) holds
 * six open-drain drive bits for the SD card lines and reads back the line levels,
 * the AND of the host's drive and the card's (sdcard.c).  Offset 12 (the old USERIO)
 * has no register.
 *
 * AUDIO (spec rev 5) loads an 8-bit rotating shift register whose bit 7 is the
 * audio pin.  CPLD2 rotates it left at the HSYNC leading edge and then every 24
 * bus slots (PDM_BIT_CLOCKS CPU clocks); the counter restarts at HSYNC, so the
 * 8th timed rotation never happens and the HSYNC rotation takes its place.  A
 * write replaces the register at once and suppresses a rotation at the same
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#define W1C_MASK  (INTSTAT_VBLANK | INTSTAT_HSYNC | INTSTAT_PS2ERR)
#define INTEN_MASK (INTEN_VBLANK | INTEN_HSYNC | INTEN_PS2 | INTEN_DUART)
#define SDIO_OUT_MASK (SDIO_DAT3 | SDIO_CLK | SDIO_CMD | SDIO_DAT0 | SDIO_DAT1 | SDIO_DAT2)
#define GPIO_MASK (GPIO_PS2CLK | GPIO_PS2DAT | GPIO_LED0 | GPIO_LED1)   /* bit 2 retired in rev 5 */

/* PDM audio shifter */
#define PDM_BIT_CLOCKS (24 * SLOT_CPU_CLOCKS)   /* 96 CPU clocks per bit, 8 bits per line */
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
